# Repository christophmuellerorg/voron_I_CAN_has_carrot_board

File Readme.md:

# What is this?

A small adapter board containing a CAN transceiver which directly plugs into the FYSETC ERB or the BTT SKR Pico to allow for use via CAN.

Warning: This is alpha quality at best and I have not yet received the ordered prototypes for verification

# License

http://solderpad.org/licenses/SHL-2.1/

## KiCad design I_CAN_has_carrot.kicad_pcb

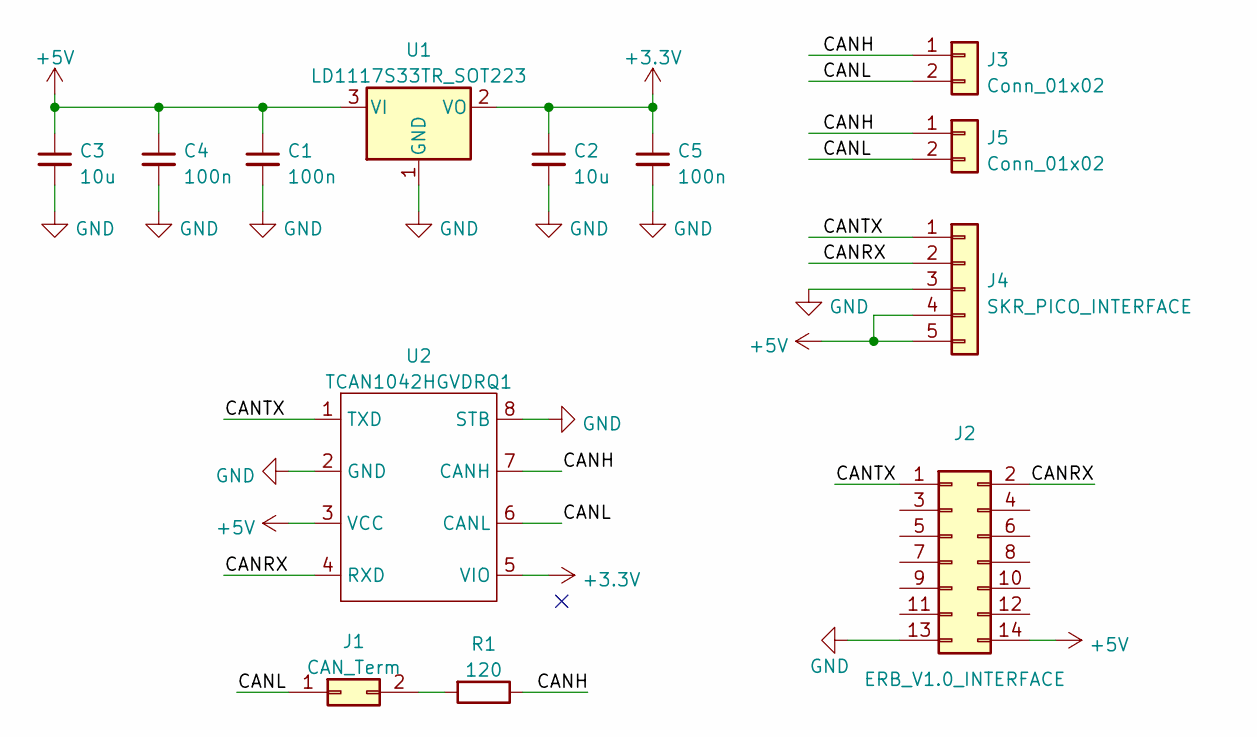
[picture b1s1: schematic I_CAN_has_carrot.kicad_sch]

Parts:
C1, C4, C5: 100n; C_0603_1608Metric; LCSC C1590
C2, C3: 10u; C_0603_1608Metric; LCSC C1691
J1: CAN_Term; PinHeader_1x02_P2.54mm_Vertical; LCSC C124375
J2: ERB_V1.0_INTERFACE; PinSocket_2x07_P2.54mm_Vertical; LCSC C38844
J3, J5: Conn_01x02; PinHeader_1x02_P2.54mm_Horizontal; LCSC C492410
J4: SKR_PICO_INTERFACE; PinHeader_1x05_P2.54mm_Vertical; LCSC C124379
R1: 120; R_0603_1608Metric; LCSC C2907096
U1: LD1117S33TR_SOT223; SOT-223-3_TabPin2; LCSC C35879
U2: TCAN1042HGVDRQ1; SOIC-8_3.9x4.9mm_P1.27mm; LCSC C132550

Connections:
+3.3V: C2.1, C5.1, U1.2 (VO), U2.5 (VIO)
+5V: C1.1, C3.1, C4.1, J2.14, J4.4, J4.5, U1.3 (VI), U2.3 (VCC)
/CANH: J3.1, J5.1, R1.1, U2.7 (CANH)
/CANL: J1.1, J3.2, J5.2, U2.6 (CANL)
/CANRX: J2.2, J4.2, U2.4 (RXD)
/CANTX: J2.1, J4.1, U2.1 (TXD)
GND: C1.2, C2.2, C3.2, C4.2, C5.2, J2.13, J4.3, U1.1 (GND), U2.2 (GND), U2.8 (STB)
unnamed: J1.2, R1.2

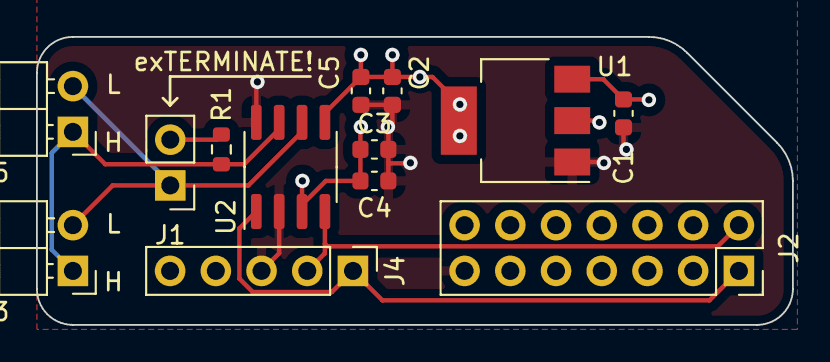
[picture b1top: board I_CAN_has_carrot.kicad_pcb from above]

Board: 4 copper layers, 42.0 x 16.0 mm, 13 parts (0 on the bottom side), 8 nets.

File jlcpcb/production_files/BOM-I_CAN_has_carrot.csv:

Comment,Designator,Footprint,LCSC
CAN_Term,J1,PinHeader_1x02_P2.54mm_Vertical,C124375
SKR_PICO_INTERFACE,J4,PinHeader_1x05_P2.54mm_Vertical,C124379
TCAN1042HGVDRQ1,U2,SOIC-8_3.9x4.9mm_P1.27mm,C132550
100n,"C1,C4,C5",C_0603_1608Metric,C1590
10u,"C2,C3",C_0603_1608Metric,C1691
120,R1,R_0603_1608Metric,C22787
LD1117S33TR_SOT223,U1,SOT-223-3_TabPin2,C35879
ERB_V1.0_INTERFACE,J2,PinSocket_2x07_P2.54mm_Vertical,C38844
Conn_01x02,"J3,J5",PinHeader_1x02_P2.54mm_Horizontal,C492410

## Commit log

2023-01-15 first prototype version
